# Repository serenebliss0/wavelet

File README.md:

<p align="center">
  <b>A modular, open-source smart speaker platform built around the ESP32 ecosystem.</b>
</p>

---

## Overview

Wavelet is a family of ESP32-based smart speakers built from a single shared codebase.

Each model targets a different use case, from a compact BLE-enabled desktop speaker to a future high-power smart speaker, while sharing the same firmware architecture through PlatformIO environments and compile-time feature flags.

The project is currently undergoing a major rewrite focused on modular firmware, modern embedded UI with LVGL and EEZ Studio, BLE onboarding, and a Flutter companion application.

---

## The Wavelet Family

| Model | Target | Current Status |
| ------ | ------ | -------------- |
| **Wavelet Mini** | ESP32-S3 | Active development |
| **Wavelet Regular** | ESP32-WROOM-32 | Being migrated to the new architecture |
| **Wavelet Max** | ESP32-S3 | Planned |

### Wavelet Mini

The Mini is the current focus of development and serves as the foundation for the rest of the Wavelet ecosystem.

It features:

- ESP32-S3
- LVGL + EEZ Studio interface
- QR-code BLE onboarding
- Wi-Fi provisioning
- Spotify API integration
- Battery monitoring
- RTC support
- Touchscreen interface

Unlike previous versions, the Mini no longer supports Bluetooth Classic audio. Instead, it focuses on becoming a connected smart speaker controlled through the companion app.

---

### Wavelet Regular

The Regular is the original portable stereo speaker.

The firmware is currently being migrated to the new modular architecture after much of the original implementation was replaced during Mini development.

Planned features include:

- Stereo audio
- Physical controls
- Battery operation
- Companion app support

---

### Wavelet Max

The Max is the planned flagship model.

It is intended to become a wall-powered smart speaker with significantly more processing power and expanded connectivity.

Development has not yet started as the required hardware is still being acquired.

---

## Project Status

| Feature | Mini | Regular | Max |
| :-- | :--: | :--: | :--: |
| BLE Onboarding | ✓ | Planned | Planned |
| LVGL + EEZ Studio | ✓ | N/A | N/A |
| Companion App Pairing | ✓ | Planned | Planned |
| Wi-Fi Provisioning | ✓ | N/A | Planned |
| Physical Buttons | In Progress | In Progress | Planned |
| Battery Monitoring | In Progress | Untested | N/A |
| Spotify API | In Progress | N/A | Planned |
| Bluetooth Audio | N/A | Broken (rewrite in progress) | N/A |
| OTA Updates | Planned | Planned | Planned |
| Clock Faces | Planned | N/A | N/A |

---

## Gallery

### Wavelet Mini UI

---

## Repository Structure

```text
esp32-smart-speaker/
├── assets/
├── data/
├── esp32-smart-speaker-schema/
├── include/
├── lib/
├── src/
│   ├── audio/
│   ├── ble/
│   ├── core/
│   ├── input/
│   ├── mini/
│   ├── screens/
│   ├── spotify_controller/
│   ├── storage/
│   ├── web/
│   ├── wifi/
│   └── main.cpp
├── spk-sounds/
├── test/
├── wavelet_app/          Flutter companion app (Git submodule)
├── webpage_iterations/
└── platformio.ini
```

---

## Getting Started

Clone the repository together with the companion app submodule.

```bash
git clone --recursive https://github.com/serenebliss0/wavelet.git
```

If you've already cloned the repository:

```bash
git submodule update --init --recursive
```

Install PlatformIO if needed.

```bash
pip install platformio
```

Build the desired firmware:

```bash
pio run -e mini
```

or

```bash
pio run -e regular
```

or

```bash
pio run -e max
```

Upload to your board:

```bash
pio run -t upload -e mini
```

---

## Roadmap

### Wavelet Mini

- [x] QR BLE onboarding
- [x] LVGL integration
- [x] EEZ Studio integration
- [x] Companion app pairing
- [x] Wi-Fi provisioning
- [ ] Clock faces
- [x] Spotify interface
- [ ] Battery management
- [ ] Settings pages

### Wavelet Regular

- [ ] Restore Bluetooth audio
- [ ] Migrate to new architecture
- [ ] Companion app support

### Wavelet Max

- [ ] Hardware prototype
- [ ] Firmware foundation
- [ ] Network services
- [ ] OTA updates
- [ ] Smart home integration

---

## Companion Application

Wavelet includes a Flutter companion application used for:

- Onboarding
- BLE pairing
- Wi-Fi setup
- Device management
- Future firmware updates

The app lives in its own repository and is included here as a Git submodule.

**Repository:** https://github.com/serenebliss0/wavelet-app

---

## Built With

- C++
- Arduino Framework
- PlatformIO
- LVGL 8.4
- EEZ Studio
- NimBLE
- ArduinoJson
- Flutter
- Dart

---

## Contributing

Contributions, suggestions and bug reports are always welcome.

If you have ideas or improvements, feel free to open an issue or submit a pull request.

---

## License

MIT License

---

Made with ❤️ by **Semire Ajayi**

## Figma Designs

---

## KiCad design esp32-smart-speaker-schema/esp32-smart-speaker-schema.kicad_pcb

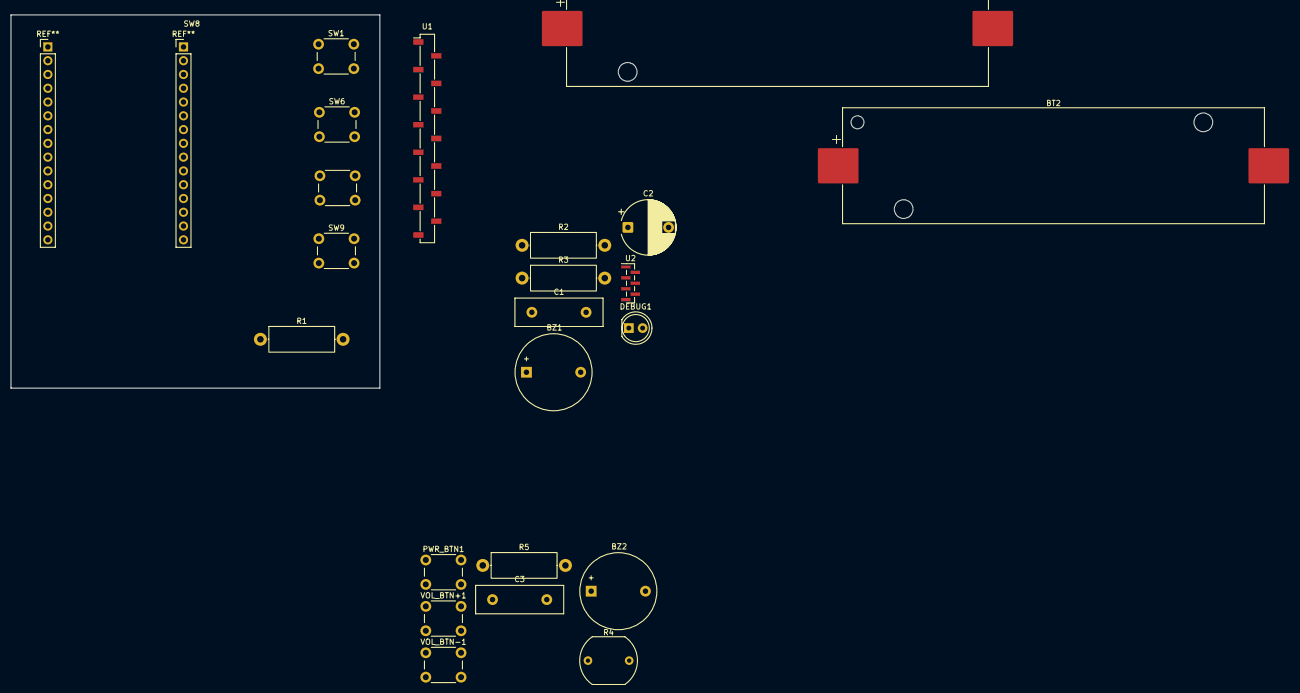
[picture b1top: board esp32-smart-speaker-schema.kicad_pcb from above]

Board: 2 copper layers, 68.0 x 68.8 mm, 22 parts (0 on the bottom side), 8 nets, no tracks yet.

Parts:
BT1, BT2: Battery; BatteryHolder_Keystone_1042_1x18650
BZ1, BZ2: Buzzer; Buzzer_D14mm_H7mm_P10mm
C1: C; C_Disc_D16.0mm_W5.0mm_P10.00mm
C2: C_Polarized; CP_Radial_D10.0mm_P7.50mm
C3: 100n; C_Disc_D16.0mm_W5.0mm_P10.00mm
DEBUG1: LED; LED_D5.0mm
PWR_BTN1: SW_Push; SW_PUSH_6mm
R1: 220; R_Axial_DIN0414_L11.9mm_D4.5mm_P15.24mm_Horizontal
R2, R3, R5: 10k; R_Axial_DIN0414_L11.9mm_D4.5mm_P15.24mm_Horizontal
R4: LDR03; R_LDR_10x8.5mm_P7.6mm_Vertical
SW1: PAUS_BTN; SW_PUSH_6mm
SW6: PWR_BTN; SW_PUSH_6mm
SW8: PREV_BTN; SW_PUSH_6mm
SW9: NXT_BTN; SW_PUSH_6mm
U1: PinSocket_1x15_P2.54mm_Vertical_SMD_Pin1Left
U2: MAX98357A; PinHeader_1x07_P1.00mm_Vertical_SMD_Pin1Left
VOL_BTN+1: SW_Push; SW_PUSH_6mm
VOL_BTN-1: SW_Push; SW_PUSH_6mm

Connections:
+5V: C1.1, C2.1, DEBUG1.2 (A), U2.4 (~SD_MODE), U2.7 (VDD)
/BAT_LEVEL: R2.2, R3.2, U1.11 (GPIO35)
/BUZZER: BZ1.1 (+), U1.6 (GPIO27)
/PAUS_BTN: SW1.1, U1.3 (GPIO13)
/Wavelet Mini/3.3V: C3.1, R4.2
/Wavelet Mini/GPIO3: R4.1, R5.2
GND: BZ1.2 (-), BZ2.2 (-), C1.2, C2.2, C3.2, PWR_BTN1.2, R1.2, R2.1, R3.1, R5.1, SW1.2, SW6.2, SW8.2, SW9.2, U1.2 (GND), U2.2 (GAIN_SLOT), U2.3 (GND), VOL_BTN+1.2, VOL_BTN-1.2
unnamed: DEBUG1.1 (K), R1.1
